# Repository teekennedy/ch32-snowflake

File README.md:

# CH32 Snowflake

A holiday snowflake with RGB LEDs, driven by the infamous CH32V003 microcontroller.

This is my first ever PCB design, and I borrowed heavily from [ch32-fireplace](https://github.com/johanwheeler/ch32-fireplace/tree/main) for snippets of schematic and code.

## PCB Shape

The snowflake shape was designed in OpenSCAD using the [BOSL2 library](https://github.com/BelfrySCAD/BOSL2).
If you want to view or make changes to the shape, I highly recommend installing the nightly version of openSCAD.

## KiCad Project

The KiCad project was designed with help from the [jlcpcb-tools plugin](https://github.com/Bouni/kicad-jlcpcb-tools).
If you plan to send this board to JLCPCB, be sure to import [corrections.csv](./board/jlcpcb/corrections.csv) before generating your pick and place file.
It has corrections for both the CH32V003 (90 degrees CCW rotation) and the TPS61002 boost converter (which is offset from where it should be).

I did my best to choose Basic parts where possible, to help keep the cost of the economic PCB assembly down.
Then I went with an ENIG coating and couldn't use economic PCBA anyway. Oh well.

## Panel (Edge Rails)

[snowflake-panel.kicad_pcb](./board/snowflake-panel.kicad_pcb) panelizes the snowflake PCB with breakaway edge rails.
It's generated using [make_panel.py](./board/tools/make_panel.py), which takes [snowflake.kicad_pcb](./board/snowflake.kicad_pcb) as input.
Re-run the script to update the panel after changing the board:

```sh
cd board
uv run tools/make_panel.py   # or just ./tools/make_panel.py
```

The script declares its dependencies inline, so [uv](https://docs.astral.sh/uv/) installs them on the fly.
It then refills the copper zones using KiCad's bundled Python, found at the default macOS install path (set `KICAD_PYTHON` to point elsewhere).

How the panel is built:

- Start with a rectangle that is as tall and wide as the snowflake and add 5 mm rails on the left and right. Take the edge cut of the snowflake, grow the outline by 2 mm, then subtract it from the rectangle.
- Add 12 tabs to connect the edge rail sections to the panel with mouse bites.
  The tabs meet the snowflake at similar angles for easier removal.
- The mouse-bite holes sit just outside the snowflake's edge so that after removal they can be filed flush for a flawless finish.
- JLCPCB tooling holes and fiducials in the rail corners.
  Everything the script adds is excluded from the BOM and pick-and-place files, so those don't change.

Generate the fabrication files from the panel, and choose "Panel by Customer" when ordering.

## Silkscreen Art (Silk Router 30°)

[board/tools/silk-router](./board/tools/silk-router/index.html) is a small browser tool for drawing trace-style silkscreen art that snaps to 30° angles (KiCad's router only does 45°).
It loads the `.kicad_pcb` as a background and treats the board edge, holes, exposed pads and existing silkscreen as obstacles for walk-around routing.

```sh
cd board
python3 -m http.server 8000   # then open http://localhost:8000/tools/silk-router/
```

Serving it this way auto-loads `snowflake.kicad_pcb`. Opening `index.html` directly also works; use "Load board…" in that case.
Export either:

- **SVG**: coordinates are in board millimetres. In KiCad use File → Import → Graphics, pick F.SilkS and place it at X 0, Y 0.
- **.kicad_mod**: a footprint whose origin is the symmetry center (150, 150 by default). Place it at that position with rotation 0.

## Firmware

In order to flash the firmware, you need to setup your build environment for [ch32fun](https://github.com/cnlohr/ch32fun).
See [their installation wiki](https://github.com/cnlohr/ch32fun/wiki/Installation) for instructions.

Next, build the `minichlink` utility.
Ensure the ch32fun submodule is initialized `git submodule update --init`.
Then, from the software/ch32fun/minichlink directory, run `make`.
If you have your RISC-V toolchain installed properly, it should build.

Now you can go to the software/src directory and run `make` to compile and flash the binary.

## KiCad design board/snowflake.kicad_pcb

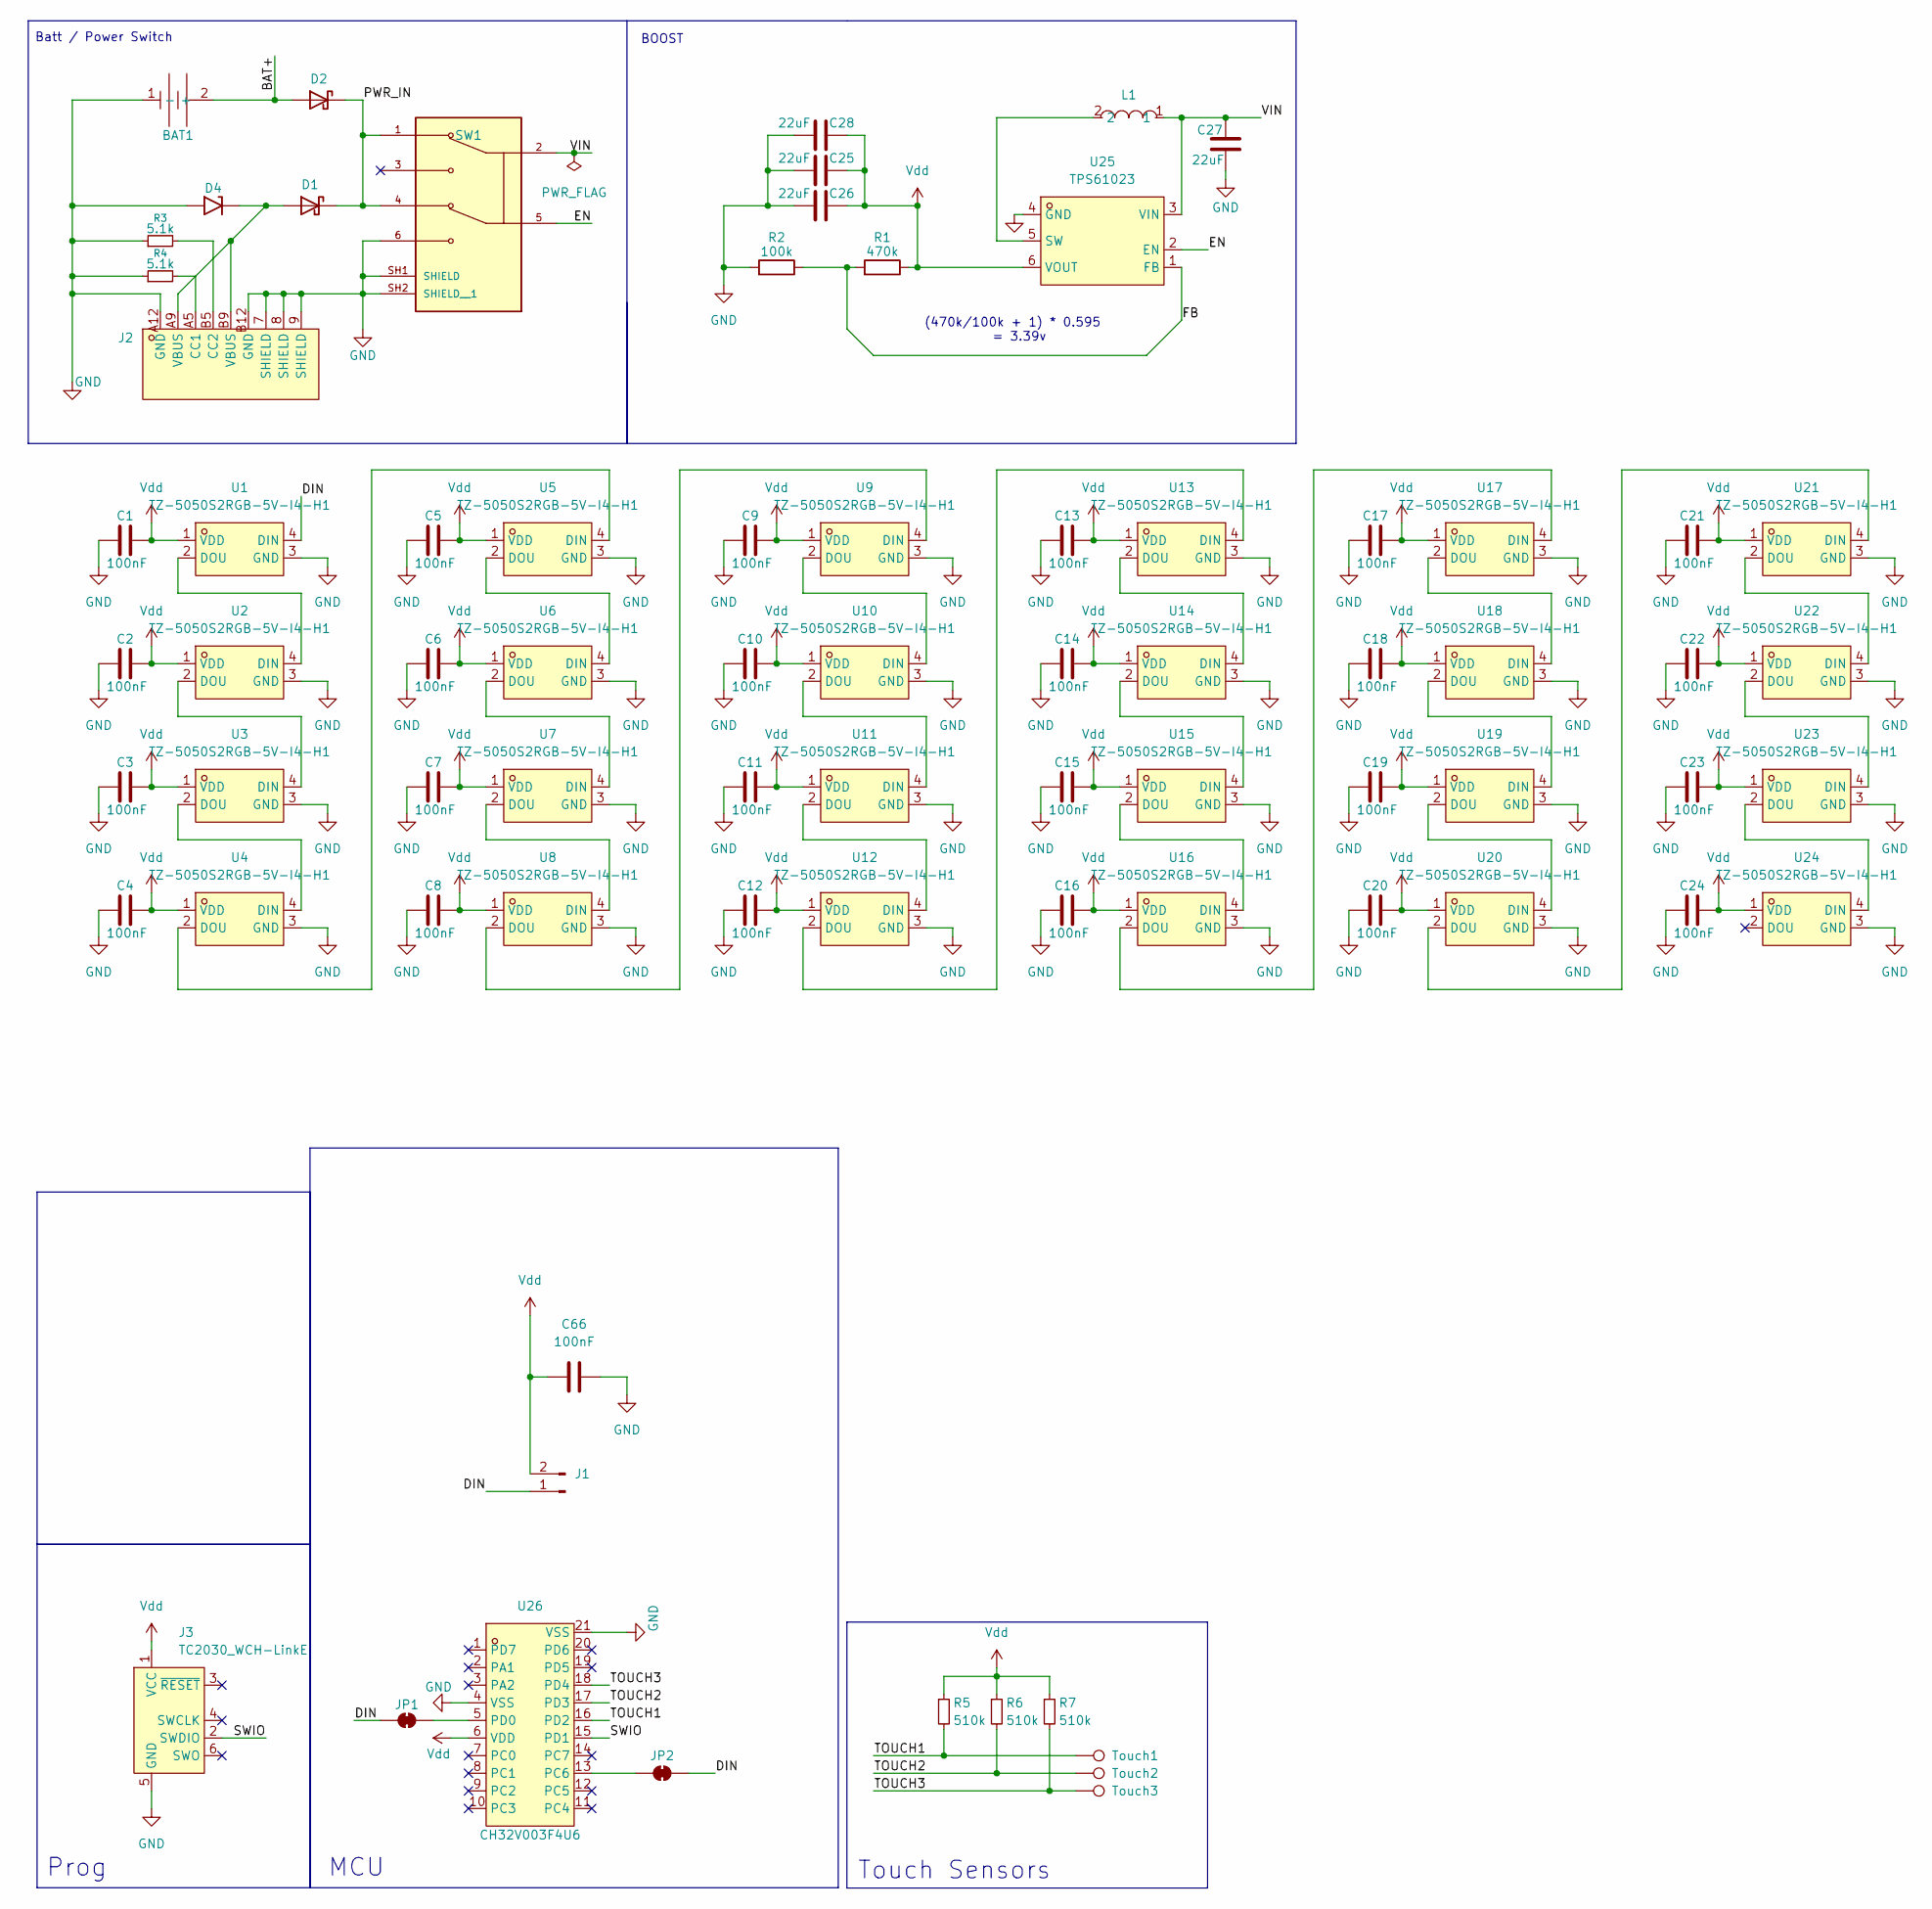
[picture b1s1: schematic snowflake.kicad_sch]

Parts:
BAT1: 2462; BAT-TH_2P-P14.50_2462; MPN 2462; LCSC Part C3029547
C1, C2, C3, C4, C5, C6, C7, C8, C9, C10, C11, C12, C13, C14, C15, C16, C17, C18, C19, C20, C21, C22, C23, C24, C66: 100nF; C_0603_1608Metric; LCSC C14663
C25, C26, C27, C28: 22uF; C_0805_2012Metric; LCSC C45783
D1, D2: B5817W; SOD-123_L2.6-W1.7-LS3.5-RD; LCSC C7420328
D4: SMF6V0A; D_SMF; LCSC C19077499
J1: Conn_01x02_Pin; PinHeader_1x02_P2.54mm_Vertical_No_Silkscreen
J2: USB_C_Receptacle_PowerOnly_6P; TYPE-C-SMD_T16-000X; MPN TYPE-C 6P LTH10.0; LCSC C5187465
J3: TC2030_WCH-LinkE; Tag-Connect_TC2030-IDC-NL_2x03_P1.27mm_Vertical
JP1, JP2: SolderJumper_2_Bridged; SolderJumper-2_P1.3mm_Bridged_RoundedPad1.0x1.5mm_No_Silksc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
L1: FWP252012P-1R0ML; IND-SMD_L2.5-W2.0_YXMBL252010P; MPN FWP252012P-1R0ML; LCSC C5179444
R1: 470k; R_0603_1608Metric; LCSC C23178
R2: 100k; R_0402_1005Metric; LCSC C25741
R3, R4: 5.1k; R_0402_1005Metric; LCSC C25905
R5, R6, R7: 510k; R_0603_1608Metric; MPN C23203; LCSC C23192
SW1: SW_Push_DPDT; SW_SWS045-030R22TSK_REVA; PARTREV A
TP5: Touch1; TouchPad_Next
TP6: Touch2; TouchPad_Loop
TP7: Touch3; TouchPad_Brightness
U1, U2, U3, U4, U5, U6, U7, U8, U9, U10, U11, U12, U13, U14, U15, U16, U17, U18, U19, U20, U21, U22, U23, U24: TZ-5050S2RGB-5V-I4-H1; LED-SMD_4P-L5.0-W5.0-TL_WS2812B-B; MPN TZ-5050S2RGB-5V-I4-H1; LCSC C26167850
U25: TPS61023; SOT-563; MPN TPS61023DRLR; LCSC C919459
U26: CH32V003F4U6; QFN-20_L3.0-W3.0-P0.40-TL-EP1.7; MPN CH32V003F4U6; LCSC C5299908

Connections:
/BAT+: BAT1.2 (+), D2.2 (A)
/DIN: J1.1, JP1.1 (A), JP2.2 (B), U1.4 (DIN)
/EN: SW1.5, U25.2 (EN)
/FB: R1.2, R2.1, U25.1 (FB)
/PWR_IN: D1.1 (K), D2.1 (K), SW1.1, SW1.4
/SWIO: J3.2 (SWDIO), U26.15 (PD1)
/TOUCH1: R5.2, TP5.1, U26.16 (PD2)
/TOUCH2: R6.2, TP6.1, U26.17 (PD3)
/TOUCH3: R7.2, TP7.1, U26.18 (PD4)
/VIN: C27.1, L1.1, SW1.2, U25.3 (VIN)
GND: BAT1.1 (-), C1.1, C2.1, C3.1, C4.1, C5.1, C6.1, C7.1, C8.1, C9.1, C10.1, C11.1, C12.1, C13.1, C14.1, C15.1, C16.1, C17.1, C18.1, C19.1, C20.1, C21.1, C22.1, C23.1, C24.1, C25.2, C26.2, C27.2, C28.2, C66.2, D4.2 (A2), J2.7 (SHIELD), J2.8 (SHIELD), J2.9 (SHIELD), J2.A12 (GND), J2.B12 (GND), J3.5 (GND), R2.2, R3.1, R4.1, SW1.6, SW1.SH1 (SHIELD), SW1.SH2 (SHIELD__1), U1.3 (GND), U2.3 (GND), U3.3 (GND), U4.3 (GND), U5.3 (GND), U6.3 (GND), U7.3 (GND), U8.3 (GND), U9.3 (GND), U10.3 (GND), U11.3 (GND), U12.3 (GND), U13.3 (GND), U14.3 (GND), U15.3 (GND), U16.3 (GND), U17.3 (GND), U18.3 (GND), U19.3 (GND), U20.3 (GND), U21.3 (GND), U22.3 (GND), U23.3 (GND), U24.3 (GND), U25.4 (GND), U26.4 (VSS), U26.21 (VSS)
unnamed: D1.2 (A), D4.1 (A1), J2.A9 (VBUS), J2.B9 (VBUS)
unnamed: J2.A5 (CC1), R4.2
unnamed: J2.B5 (CC2), R3.2
unnamed: JP1.2 (B), U26.5 (PD0)
unnamed: JP2.1 (A), U26.13 (PC6)
unnamed: U1.2 (DOU), U2.4 (DIN)
unnamed: U2.2 (DOU), U3.4 (DIN)
unnamed: U3.2 (DOU), U4.4 (DIN)
unnamed: U4.2 (DOU), U5.4 (DIN)
unnamed: U5.2 (DOU), U6.4 (DIN)
unnamed: U6.2 (DOU), U7.4 (DIN)
unnamed: U7.2 (DOU), U8.4 (DIN)
unnamed: U8.2 (DOU), U9.4 (DIN)
unnamed: U9.2 (DOU), U10.4 (DIN)
unnamed: U10.2 (DOU), U11.4 (DIN)
unnamed: U11.2 (DOU), U12.4 (DIN)
unnamed: U12.2 (DOU), U13.4 (DIN)
unnamed: U13.2 (DOU), U14.4 (DIN)
unnamed: U14.2 (DOU), U15.4 (DIN)
unnamed: U15.2 (DOU), U16.4 (DIN)
unnamed: U16.2 (DOU), U17.4 (DIN)
unnamed: U17.2 (DOU), U18.4 (DIN)
unnamed: U18.2 (DOU), U19.4 (DIN)
unnamed: U19.2 (DOU), U20.4 (DIN)
unnamed: U20.2 (DOU), U21.4 (DIN)
unnamed: U21.2 (DOU), U22.4 (DIN)
unnamed: U22.2 (DOU), U23.4 (DIN)
unnamed: U23.2 (DOU), U24.4 (DIN)
unnamed: L1.2, U25.5 (SW)
Vdd: C1.2, C2.2, C3.2, C4.2, C5.2, C6.2, C7.2, C8.2, C9.2, C10.2, C11.2, C12.2, C13.2, C14.2, C15.2, C16.2, C17.2, C18.2, C19.2, C20.2, C21.2, C22.2, C23.2, C24.2, C25.1, C26.1, C28.1, C66.1, J1.2, J3.1 (VCC), R1.1, R5.1, R6.1, R7.1, U1.1 (VDD), U2.1 (VDD), U3.1 (VDD), U4.1 (VDD), U5.1 (VDD), U6.1 (VDD), U7.1 (VDD), U8.1 (VDD), U9.1 (VDD), U10.1 (VDD), U11.1 (VDD), U12.1 (VDD), U13.1 (VDD), U14.1 (VDD), U15.1 (VDD), U16.1 (VDD), U17.1 (VDD), U18.1 (VDD), U19.1 (VDD), U20.1 (VDD), U21.1 (VDD), U22.1 (VDD), U23.1 (VDD), U24.1 (VDD), U25.6 (VOUT), U26.6 (VDD)

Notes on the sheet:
Batt / Power Switch
BOOST
Prog
Touch Sensors
(470k/100k + 1) * 0.595 = 3.39v
MCU

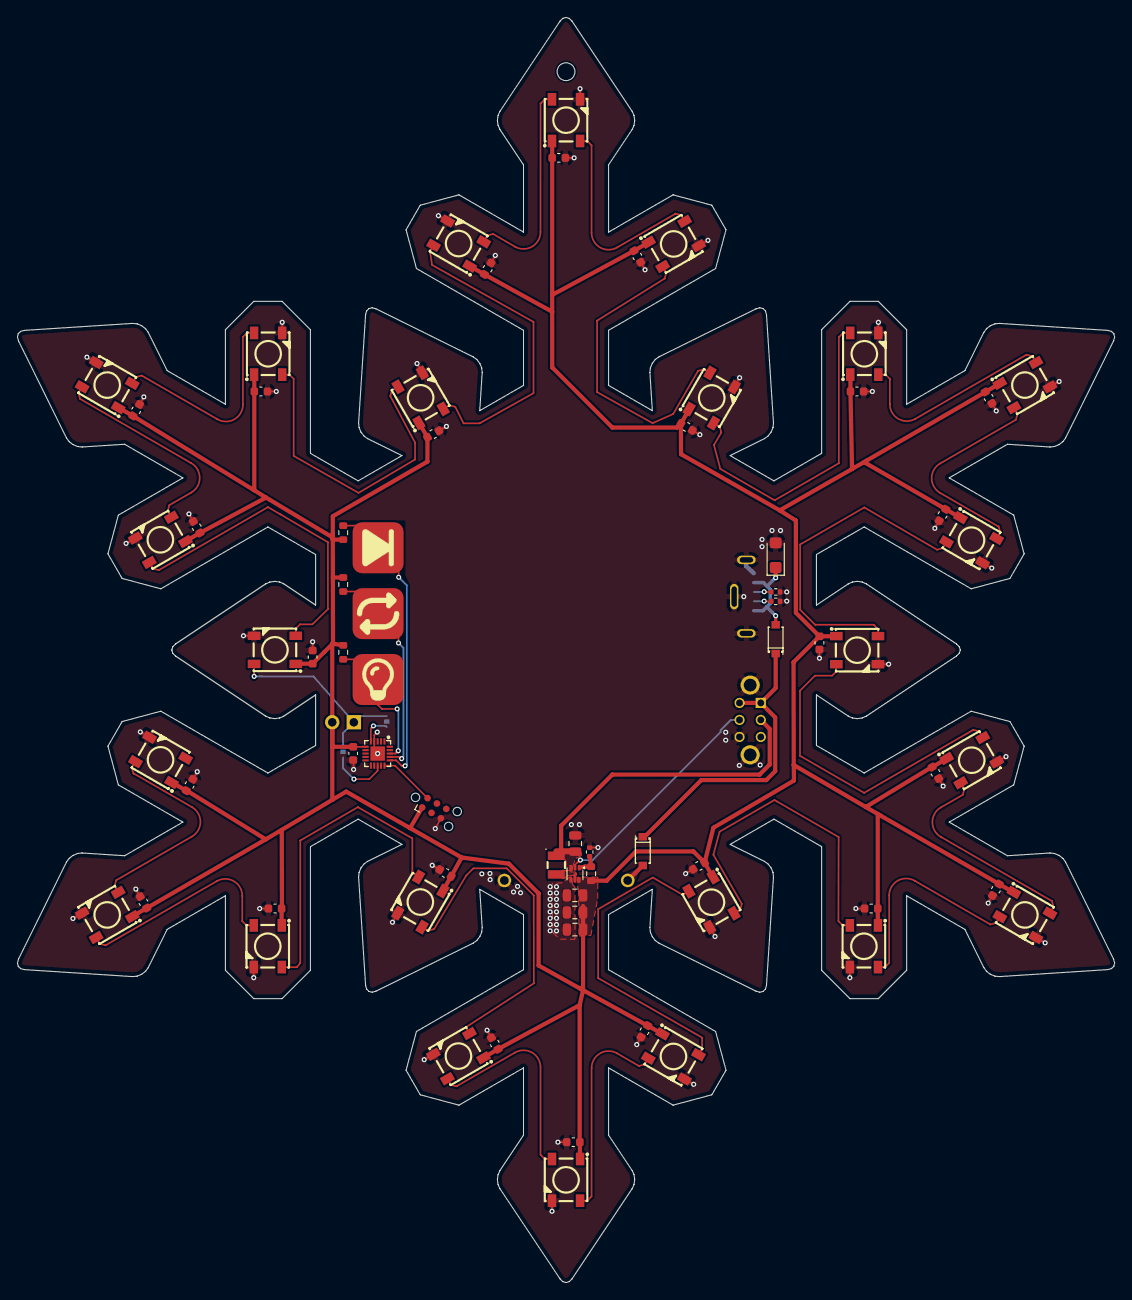
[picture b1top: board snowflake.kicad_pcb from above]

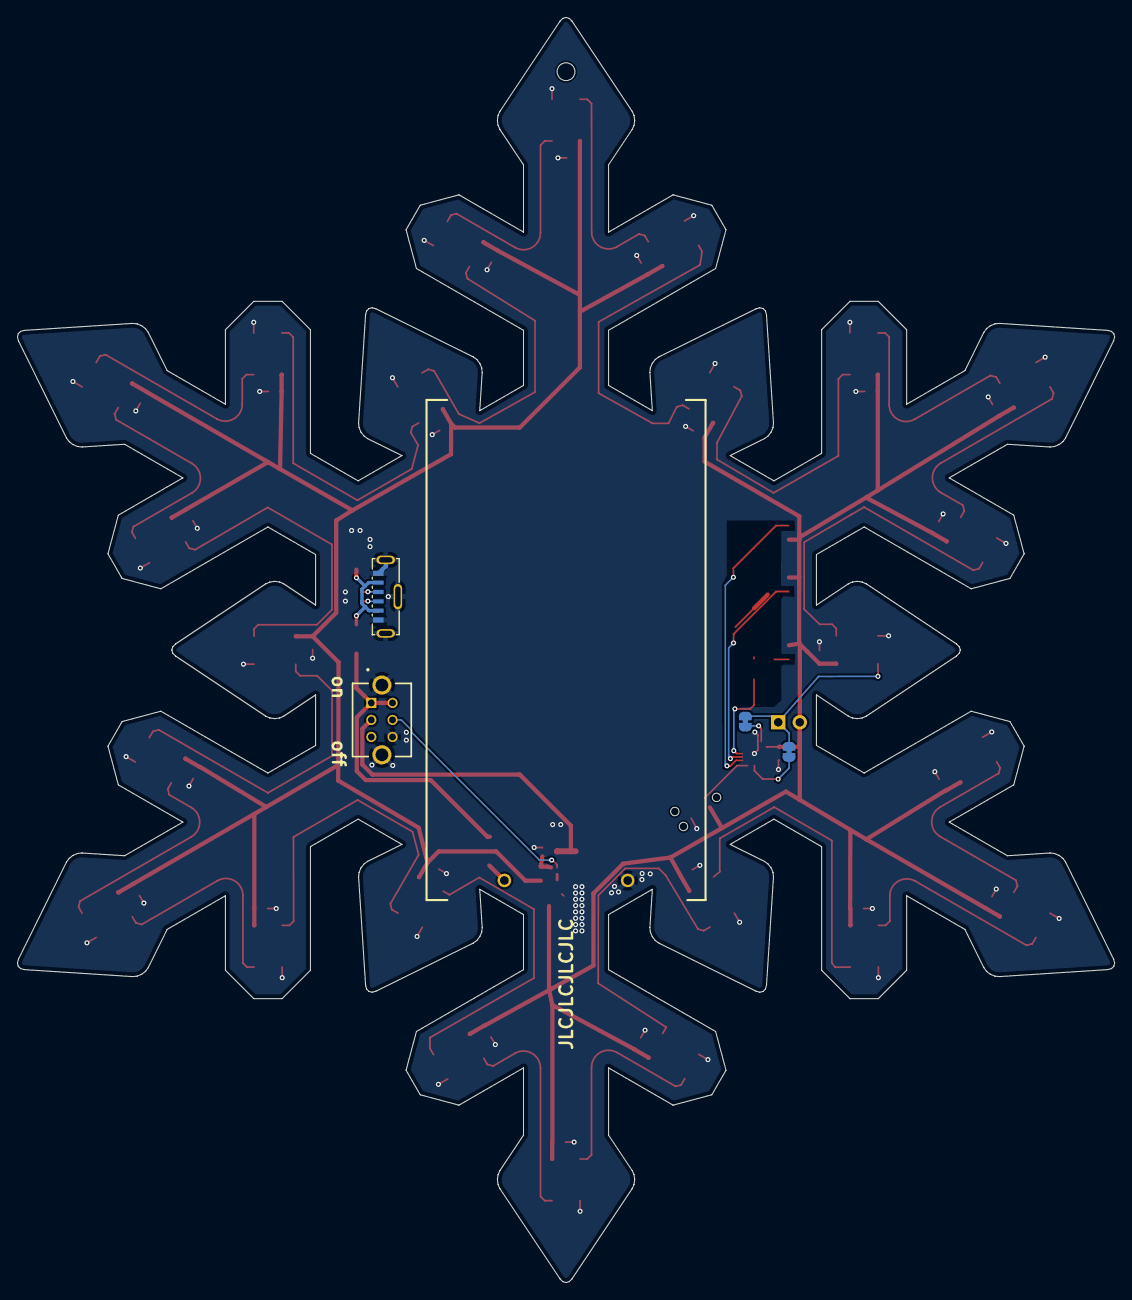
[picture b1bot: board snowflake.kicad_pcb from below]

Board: 2 copper layers, 129.0 x 148.8 mm, 77 parts (5 on the bottom side), 41 nets.

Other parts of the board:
H1: Hanging hole; HangingHole_2.1mm

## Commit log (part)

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2025-11-08 snowflake shape with evenly spaced leds
2025-11-10 v1 snowflake shape
2025-11-10 Modularize hexagon shape
2025-11-10 About to create rotational array of LEDs
2025-11-11 2/6 branches
2025-11-11 Add JLCPCB Part Numbers
2025-11-11 Submitted for cost estimate from JLCPCB
2025-11-11 The nets are happy again
2025-11-13 Use zones instead of traces for +5V
2025-11-13 First prototype
2025-11-13 Add mounting and tooling holes
2025-11-13 Use basic parts, fix boost converter positioning
2025-11-13 Add more vias to try and keep the ground planes even
2025-11-14 Add teardrops to vias and PTH pads, mask border
2025-11-14 Remove lock file, update .gitignore
2025-11-24 put everything on one side
2025-11-26 initial import of software stack
2025-11-26 Get rainbow pattern working
2025-11-26 Update PCB and customize some footprints
2025-11-26 Add readme, update rgb led driver
2025-11-30 Get CH32V003 working
2025-11-30 Cleanup
2025-12-01 Add graphics to board
2025-12-01 Final board updates before sending
2025-12-01 Catch what would have been a huge mistake
2025-12-01 Cleanup power switch traces
2025-12-01 Submitted for production
2025-12-03 Add preview image
2025-12-03 Add missing 3d file for CH32v003 footprint
2025-12-12 Got as far as I could with DMA-based LED control
2025-12-20 Fix R1 part number
2025-12-20 Add JLCPCB pick and place corrections.csv
2025-12-20 Update variables based on button press
2025-12-20 Move touch code to subfolder, fix animations crashing
2025-12-21 Tweak brightness and twinkle animation
2025-12-21 Add nvram settings, multiple twinkle animations
2025-12-21 Add shooting star animation
2025-12-21 Make frame timing consistent across animations
2025-12-21 Implement shuffle functionality
2025-12-22 Add christmas lights animation
2026-01-02 Make touch button detection more robust
2026-01-02 Add small instruction card to go with snowflake
2026-01-12 Reduce brightness, add test animation
